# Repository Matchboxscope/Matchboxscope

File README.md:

# Matchboxscope

This is a repository for the smallest standalone low-cost open-source DIY incubator-contained microscope that can be used for a gazillion different applications. Sounds interesting? Continue reading!

The core component of this device is a ESP32 microcontroller that is packed with a small Camera (OV2460) and microSD card slot, which makes it a perfect match for your microscopy project. In the most minimal version, you don't need anything but the ESP32-CAM and perhaps some chewing gum to raise the objective lens in order to create a finite corrected microscope.

However, we wanted to make the microscope a bit more practical and created some 3D printed parts that will realize the following devices:

**The Anglerfish**: This device is well preserved in your beloved jars and hence watertight. Why? Throw it in your nearby pond and collect data how microfilm grows on the jars' surface. Fun! Follow the [**BLUE PILL 🔵**](Anglerfish.md)

**The Matchboxscope**: This is a simple self-contained microscope, e.g. for tacking snapshots of your microfluidic chips, your parasite containing slides or just for fun. It comes with a minimum number of parts, but offers a spring-loaded z-stage. Also ideal for your incubator-contained microscopy experiments! Follow the [**RED PILL 🔴**](Matchboxscope.md)

**The Z-Stacker**: It adds an automatic focusing unit to the *Matchboxscope* in order to create temporal Z-stacks of your beloved cell cultures. It needs more electronics, but still relies on the ESP32-CAM only. Lots of fun, too.  Follow the [**GREEN PILL 🟢**](Matchboxscope.md)

Still curious? *Continue Reading by clicking on individual device sub-pages!*

### How to install

In order to get the code compiled and uploaded to your ESP32 camera board, a number of steps have to be carried out to prepare the system.

#### Compile and Upload

This code is written for the `AI_THINKER`

1. Download the Arduino IDE 1.8.X from [here](https://arduino.cc/)
2. Install the ESP32 IDF tool through the Arduino board manager; Add the following link to the settings (a more in-depth tutorial can be found [here](https://randomnerdtutorials.com/installing-the-esp32-board-in-arduino-ide-windows-instructions/)):
`https://raw.githubusercontent.com/espressif/arduino-esp32/gh-pages/package_esp32_dev_index.json`
When installing the board, go for the version `2.0.3`
3. (*OBSOLETE!*) Install the ESP32Cam library following this [link](https://github.com/yoursunny/esp32cam) and their README
4. Clone this repository
5.
* *MatchBoxscope*: Choose the latest release for the MatchBoxscope, open the `.ino` and flash the project ([v0.1](https://github.com/beniroquai/Matchboxscope/releases/download/Matchboxscope/ESP32CAM-MatchBoxScope-MAIN.zip))
* *Anglerfish*: We will provide a ready-to-use software solution soon
* *IncubatorMicroscope*: We will provide a ready-to-use software solution soon
6. *Compiling*: Under `Tools`select your board (`DEV Module`), `port` and enable the `PSRAM` enable 4MB external PSRAM.
7. Compile and Upload

**ATTENTION for Android users:** The Wi-Fi in access point mode (*AP*) does not offer internet, hence Android uses available cellular/mobile data and won't open the local address (`192.168.4.1`). *Solution:* Switch off mobile data or disable `Wifi+`

**Wi-Fi settings:**

Please have a look in the Wi-Fi settings to adjust them according to your network configuration:

`cpp
boolean hostWifiAP = true; // set this variable if you want the ESP32 to be the host
const char* mSSID = "Blynk";
const char* mPASSWORD = "12345678";
const char* mSSIDAP = "Matchboxscope";
``

#### Upload files to SPIFFs

For the `HTML` and `CSS` files, you can upload the files to

# Software

## Anglerfish Code

Getting many images in an autonomous "diving" experiment is key. For this, we wrote a firmware that enables you to find the focus and as soon as you're done, the microcontroller goes into deep-sleep mode to save energy. The following steps are important to carry out before your experiment.

**The protocol**
1. Assemble unit and charge battery
2. Upload software and insert SD card
3. Then connect the battery to ESP32 and watch the camera stream via Wi-Fi and adjust the focus so that you can see the surface (of the jar) in focus. That's what the screws and springs are for. You do this once.
4. Either with a switch (awkward, because you have to solder), or via Wi-Fi (switch in Webgui/HTTP endpoint), deactivate the focus mode.
5. Microscope goes into deep-sleep mode and wakes up every `X` minutes to take a photo and save it on the SD card.

In the deep-sleep setting, it consumes virtually no power.

**Problem/thoughts:**
- It is not possible to detect whether it is deep-sleep or disconnected from the power supply, so we built in this funny construct with the date/time of flashing the ESP32. So you can reset the EEPROM variable for focus mode (yes/no) when you (re-)flash the microcontroller
- the SD card and the LED flash hinder each other a bit because they both run on the same pins (yup). But I think we managed to get everything working by relying on the 1-bit mode of the SD card (slower, but more stable); also important: Initialize the SD card before any GPIO assignment (i.e. in `setup()`)
- The same code could also be used in an incubator-contained microscope, for example, to observe the growth of cells. But for this it would be important to keep the Wi-Fi stream running :)

# Videos

That's the software for the Matchboxscope:

And a more in-detail tutorial on how to use the software:

## Get Involved

This project is open so that anyone can get involved. You don't even have to learn CAD designing or programming. Find ways you can contribute in  [CONTRIBUTING](https://github.com/openUC2/UC2-GIT/blob/master/CONTRIBUTING.md)

## License and Collaboration

This project is open-source and is released under the CERN open hardware license. Our aim is to make the kits commercially available.
We encourage everyone who is using our Toolbox to share their results and ideas, so that the Toolbox keeps improving. It should serve as an easy-to-use and easy-to-access general purpose building block solution for the area of STEAM education. All the design files are generally for free, but we would like to hear from you how is it going.

You're free to fork the project and enhance it. If you have any suggestions to improve it or add any additional functions, make a pull-request or file an issue.

Please find the type of licenses [here](https://github.com/openUC2/UC2-GIT/blob/master/License.md)

REMARK: All files have been designed using Autodesk Inventor 2019 (EDUCATION)

## Collaborating
If you find this project useful, please like this repository, follow us on Twitter and cite the webpage! :-)

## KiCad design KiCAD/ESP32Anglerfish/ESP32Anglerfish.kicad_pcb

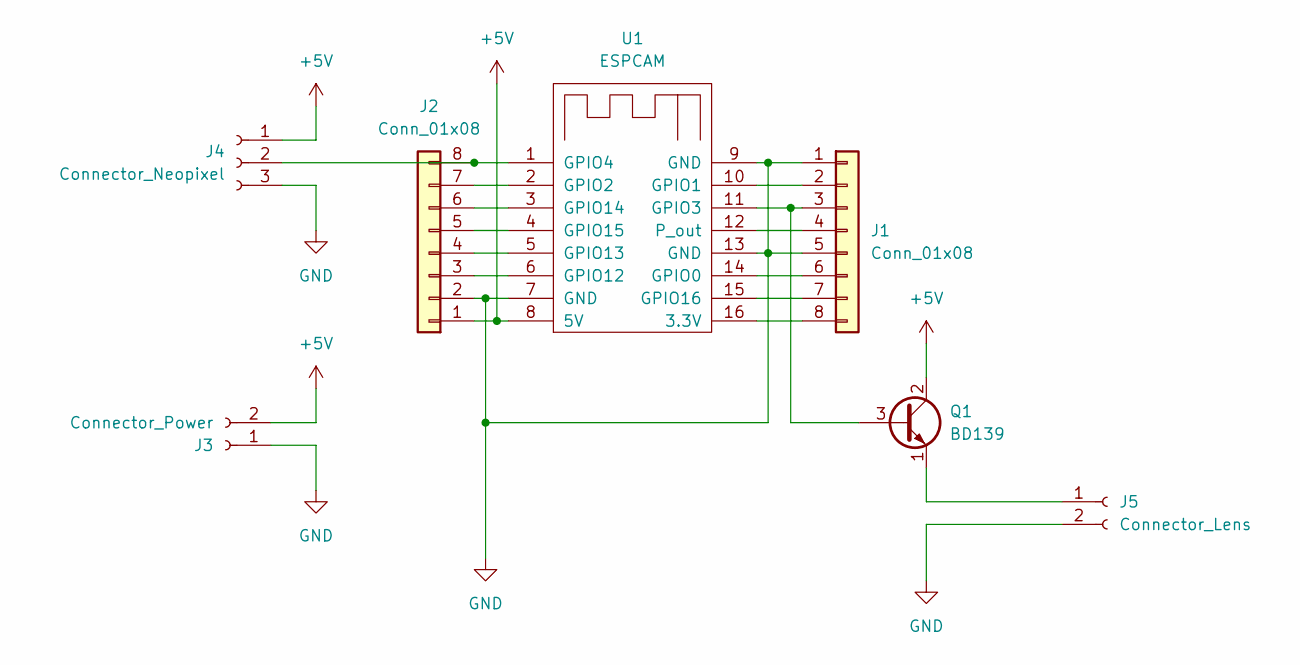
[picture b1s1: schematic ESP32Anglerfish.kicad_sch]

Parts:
J1, J2: Conn_01x08; PinSocket_1x08_P2.54mm_Vertical
J3: Connector_Power; PinSocket_1x02_P2.54mm_Vertical
J4: Connector_Neopixel; PinSocket_1x03_P2.54mm_Vertical
J5: Connector_Lens; PinSocket_1x02_P2.54mm_Vertical
Q1: BD139; TO-126-3_Vertical
U1: ESPCAM; ESPCAM_bottom

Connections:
+5V: J2.1, J3.2, J4.1, Q1.2 (C), U1.8 (5V)
GND: J1.1, J1.5, J2.2, J3.1, J4.3, J5.2, U1.7 (GND), U1.9 (GND), U1.13 (GND)
unnamed: J1.2, U1.10 (GPIO1)
unnamed: J1.3, Q1.3 (B), U1.11 (GPIO3)
unnamed: J1.4, U1.12 (P_out)
unnamed: J1.6, U1.14 (GPIO0)
unnamed: J1.7, U1.15 (GPIO16)
unnamed: J1.8, U1.16 (3.3V)
unnamed: J2.3, U1.6 (GPIO12)
unnamed: J2.4, U1.5 (GPIO13)
unnamed: J2.5, U1.4 (GPIO15)
unnamed: J2.6, U1.3 (GPIO14)
unnamed: J2.7, U1.2 (GPIO2)
unnamed: J2.8, J4.2, U1.1 (GPIO4)
unnamed: J5.1, Q1.1 (E)

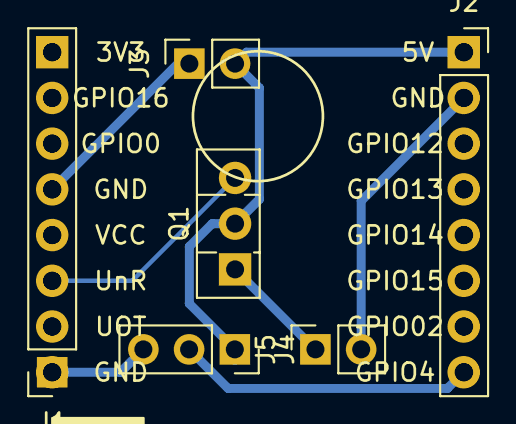
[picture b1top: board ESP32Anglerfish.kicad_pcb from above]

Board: 2 copper layers, 7 parts (0 on the bottom side), 15 nets.

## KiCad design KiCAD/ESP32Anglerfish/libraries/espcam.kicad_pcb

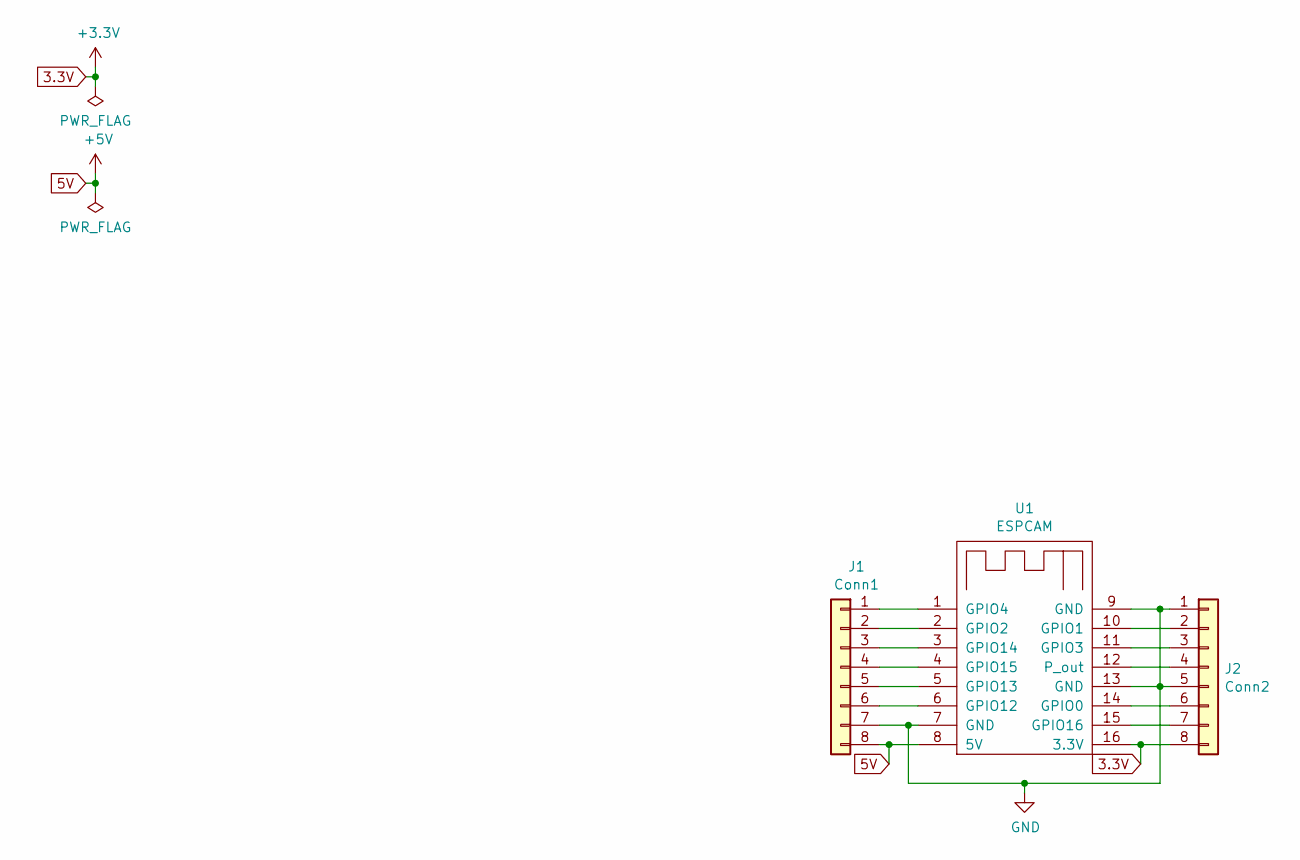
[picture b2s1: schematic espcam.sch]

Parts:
J1: Conn1; PinSocket_1x08_P2.54mm_Vertical
J2: Conn2; PinSocket_1x08_P2.54mm_Vertical
U1: ESPCAM; ESPCAM_bottom

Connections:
3.3V: J2.8, U1.16 (3.3V)
5V: J1.8, U1.8 (5V)
GND: J1.7, J2.1, J2.5, U1.7 (GND), U1.9 (GND), U1.13 (GND)
unnamed: J1.1, U1.1 (GPIO4)
unnamed: J1.2, U1.2 (GPIO2)
unnamed: J1.3, U1.3 (GPIO14)
unnamed: J1.4, U1.4 (GPIO15)
unnamed: J1.5, U1.5 (GPIO13)
unnamed: J1.6, U1.6 (GPIO12)
unnamed: J2.2, U1.10 (GPIO1)
unnamed: J2.3, U1.11 (GPIO3)
unnamed: J2.4, U1.12 (P_out)
unnamed: J2.6, U1.14 (GPIO0)
unnamed: J2.7, U1.15 (GPIO16)

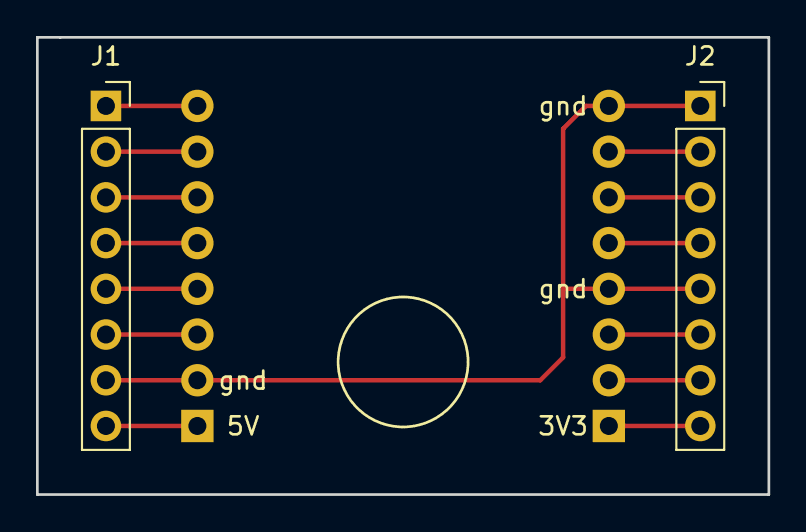
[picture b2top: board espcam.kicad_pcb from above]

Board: 2 copper layers, 40.6 x 25.4 mm, 3 parts (0 on the bottom side), 14 nets.

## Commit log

2022-02-10 Adding documentation, resorting STLs
2022-02-11 Updating STLs
2022-02-21 Cleaning up the folder
2022-02-27 Updating the software for Bootstraped frame visualization
2022-02-27 Solving problem with stream interrupt
2022-02-27 Making CSSs available offline
2022-02-27 Attempting to make the CSS files working offline
2022-03-07 updating version to v1 using m12 lens
2022-03-07 updating the stl files
2022-03-07 Update INventor file
2022-03-17 Updating stl files to v1
2022-03-17 Fixed missing hole
2022-03-20 Adding SD-card support in the code
2022-03-21 Updating to a new round and yet simpler design
2022-03-21 Updating STL files
2022-03-23 Adding abbility to let the microscope take images forever
2022-03-28 Updating to newer STL version with periscope illumination
2022-03-29 Updating some images and new STLs
2022-03-29 adding long periscope
2022-04-03 Updating software with socket-based connection to have stream + controling simultaneously
2022-04-10 Adding Anglerfish configuration
2022-04-16 Updating Anglerfish
2022-04-17 Adding Information about Anglerfish
2022-04-18 Major cleanup of the code
2022-04-19 Cleanup code directory, updating installtion instructions
2022-04-19 Fix some bugs with preferences; do first iteration of code decomposition
2022-04-19 Improve web server handler encapsulation
2022-04-19 Refactor wifi setup, allow webserver to use any FS
2022-04-19 Encapsulate image acquisition into a Camera class
2022-04-19 Adjust decomposition
2022-04-20 Updating a lot of CAD files
2022-04-23 Updating CAD files and adding processing file
2022-05-06 Adding source code for a potential incubator application
2022-05-07 Fixing bug in Android
2022-05-10 Minor changes in the incubator code
2022-05-11 Adding Stream+Control in one framework as a portotype
2022-05-13 Updating the sketch for the incubator to have stream + SD-saving options
2022-05-16 Adding a new version with sd-mode: 1 bit. Everything works now
2022-05-20 Adding new static version of the incubator microscope
2022-05-20 adding many images
2022-05-28 First glimpse of the new documentation for matchbox/anglerfish
2022-05-31 Updating assembly tutoial for anglerfish
2022-05-31 Cleaning up documenation
2022-05-31 Fixing typo
2022-06-01 Final working state for incubator-contained microscope
2022-06-01 Cleanup ESP32 code
2022-06-01 Updating
2022-06-01 Final Cleanup
2022-06-07 ADding new firmware for Matchboxscope
2022-06-07 Finalizing the first release for the Matchboxscope
2022-06-07 Finalizing software, adding documentation for Matchboxscope
2022-06-07 cleanup Code
2022-06-07 Adding timelapse feature
2022-06-12 Sample holder designs (magnets)
2022-06-12 Adding new software to have timelapse imaging
2022-06-12 Adding Json as REST
2022-06-12 Updating REST for ImSwitch
2022-06-13 Renamig current firmware to Main, adding captive portal, wifimanager, improving stream
2022-06-13 Updating some parameters; Wifi Captive handling
2022-06-13 Updating code with prefs
2022-06-13 fixing issue in pref settings
2022-06-14 Updating errors in Pref Manager; Almost done
2022-06-14 Adding ImJoy Button
2022-06-14 added build guide pictures
2022-06-14 updated build guide
2022-06-15 Fixing Anglerfish PArt
2022-06-15 Adding ability to choose effects in code.
2022-06-15 Integrate ImJoy and ImageJ.JS
2022-06-16 Makng sure stream is stopped when capturing; Fixing ImJoy issue
2022-06-16 Updating Documentation for Software
2022-06-20 Adding M12 Autofocus version
2022-06-25 Adding Autofocus to the Code - testing only
2022-07-19 Adding VCM-based autofocus
2022-07-20 Trying to use a different sensor.
2022-07-20 Update VCM setup and jar insert
2022-07-20 updating CAD
2022-07-20 update jar inlet
2022-07-21 cleaning up CAD and adding lightsource for anglerfish
2022-07-22 Minor updates in code's debugging features
2022-07-24 Adding Neopixel functionalitiy and dedicated PCB/ESP32-CAM Shield to work with LED/LENS
2022-08-04 Adding KiCad PCB for anglerfish, experimenting with NEopixel strip
2022-08-04 Fixing error with LEDCchannels?!
2022-08-09 adding OTA Server endpoints
2022-08-09 Revert "adding OTA Server endpoints"
    This reverts commit dfa9e4fdd9c9e9b8c4446fd2d1c6844a36653449.
2022-08-10 Ensuring proper OTA support for Anlgerfish/Matchboxscope
2022-08-14 cleaning up CAD
2022-09-05 Updating Anglrefish with toslink and pcb
2022-09-13 First attempt to compile binary in the cloud
2022-09-14 Adding anglerfish STLs 1.0
2022-09-14 Cleaning up for release 1.0
2022-09-21 adding toslink adapter for illuminatin (matchvoxsocpe)
2022-09-24 Enabling upload of images to a Google Drive folder
2022-09-28 update save-to-gdrive (not workig yet..image resolution?)
2022-09-29 Cleaning up the code; Implementing only necessary functions
2022-09-30 Mini adjustment in the SD-card setup to mount it properly
2022-09-30 Adding binary for OTA
2022-10-02 Bugfixing with z-stacking and deepsleep + wakeup
2022-10-02 Avoiding dual use for input/output pins
2022-10-03 enabling wake up by unplugging SD card - YAY!
2022-10-04 Adding necessary libraries for the binaries to compile
2022-10-04 Adding ESP32Ping
2022-10-16 Adding new lid, adding possibility to mount microscope in Lid instead
2022-10-16 Updaitng lid-contained Anglerfish
2022-10-16 Don't use LED while file saving
2022-10-17 Turning LENS/LED only on when taking image => save energy; SD card writing sometimes takes long (e.g. >1000 files)
2022-10-19 Ensuring high resolution is set up when taking timelapse images
2022-10-19 Cleaning up old versions
2022-10-31 Adding STLs for the new jar-contained microscope, beautifciation of the code
2022-11-02 Add README and LICENSE for the ESP32 subdirectory
2022-11-02 Add a stub for captive portal usage
2022-11-02 Improve organization of header includes and global consts & vars
2022-11-02 Apply the Arduino IDE's auto-formatter
2022-11-02 Make header files robust to multiple inclusions
2022-11-06 Adding updated STLs for toslink adapter
2022-11-10 Miro change to avoid a potential boot loop.
2023-01-30 Updating CAD files for mini planktoscope
2023-01-30 Updating latest .bin
2023-02-18 Added the magnet version
    STL for the magnet version
2023-03-19 Fix typos
2023-03-19 Typos and latex formulas
2023-03-19 Typos
2023-04-10 Added periscope LED
    STL for the periscope external LED (LIHAO LED 12mm)
2023-04-19 Cleaning up software and adding IM parts
2023-04-24 added external LED
    added update for the external LED on the matchboxscope
2023-04-24 Adding InjectionMolded Study
2023-05-01 Updating IM parts
2023-05-17 adding inline holographic microscope
2023-05-25 Temp. Backup of CAD files
2023-05-29 Adding latest CAD files for XIAO camera module
2023-06-04 Updating Anglerfish sample mounts (Inventor)
2023-06-26 updating latest Inventor files
2023-06-29 updating CAD files
